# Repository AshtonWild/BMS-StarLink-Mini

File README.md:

# 5S 26650 BMS for Starlink Mini

A battery management board for a 5-cell (5S) Li-ion 26650 pack that powers a Starlink Mini through an IP2368 USB-C charger/converter module. Designed in KiCad 10.

This board was designed specifically for the [Nexus-2 (Mounted Pack)](https://eclecticdesigns.ca/shop/p/nexus-2) from [eclecticdesigns.ca](https://eclecticdesigns.ca). Its shape, mounting holes and wire-pad positions are laid out for that pack, so check the fit before using it in anything else.

Designed by Ashton W, Eclectic Designs Inc. Board revision: **Rev 2026-11-03**.

| Bottom (components) | Top (cell wire pads) |
|---|---|
|  |  |

> **Lithium battery warning.** A 5S 26650 pack can deliver hundreds of amps into a short and can catch fire if overcharged, shorted, or charged below freezing. This is a hobby design shared as-is, with no warranty. It has not been certified or independently tested. Build and use it at your own risk, never leave a first charge unattended, and follow [docs/TESTING.md](docs/TESTING.md) before connecting real cells.

## Read this first: known issues in this revision

The design files and BOM in this repository are **Rev 2026-11-03 as drawn**. A later design review found two parts that must be substituted when you build it. Both use the existing pads; the PCB does not change.

| Part | As drawn | Fit instead | Why |
|---|---|---|---|
| **U1** | BM3451TJDC-T28A | BM3451**TNDC**-T28A or BM3451**UNDC**-T28A | The TJDC version is obsolete. The others are pin-compatible. |
| **D1** | SMCJ24CA (two-way TVS) | SMCJ24**A** (one-way TVS), **turned 180° from the board marking** | The two-way part lets the FETs see too much voltage when a short is cut off. |

**D1 orientation is safety-critical.** The cathode band must be on the pad connected to PACK+. Fitted the other way round, it shorts the pack. See [docs/ASSEMBLY.md](docs/ASSEMBLY.md).

Other limitations to know about:

- **No cold-charge protection.** The BM3451 has no low-temperature cut-off. Use the IP2368's NTC input with a thermistor on the cells.
- **TH1 is on the board, not on a cell.** Use a leaded thermistor taped to a cell instead.
- **No strain relief** for the battery wires. Glue them down after soldering.
- **No test points.** Probe on component pads.

The full review is in [docs/DESIGN_REVIEW.txt](docs/DESIGN_REVIEW.txt).

## Specifications

| | |
|---|---|
| Cells | 5 in series, Li-ion 26650 (4.2 V full) |
| Protection IC | BYD BM3451 (TSSOP-28) |
| Overcharge cut-off | 4.25 V per cell (TNDC) or 4.235 V (UNDC), 1 s delay |
| Low-voltage cut-off | 2.8 V per cell (TNDC/UNDC), 1 s delay |
| Discharge overcurrent | about 20 A (200 ms), 80 A (4.4 ms), 160 A short circuit (about 300 µs) |
| Charge overcurrent | about 10 A |
| Intended load | about 7 A continuous |
| Cell balancing | passive, about 89 mA per cell, starts at about 4.19 V |
| Over-temperature | charge off at about 45 °C, discharge off at about 62 °C (10 kΩ B3950 NTC) |
| Fuse | Littelfuse 0456025.ER, 25 A, on the positive output |
| Power FETs | 2 × Vishay SiR638ADP (40 V), low side, back to back |
| Current sense | 5 mΩ, 3 W, Kelvin connected |
| Board | 2 layers, 2 oz copper, 1.6 mm, about 155 × 85 mm overall, 4 × M3 holes |

Trip currents come from the BM3451 datasheet thresholds and the 5 mΩ sense resistor; allow about ±15–20%.

## Repository layout

```
hardware/     KiCad 10 project (schematic, PCB, custom footprints, design rules)
production/   Gerbers, BOM and placement file as sent to JLCPCB
docs/         Schematic PDF, board prints, assembly guide, test procedure, design review
```

| File | What it is |
|---|---|
| `hardware/BMS StarLink Mini.kicad_pro` | Open this in KiCad 10 |
| `production/BMS_StarLink_Mini_Gerbers_JLCPCB.zip` | Gerber and drill files |
| `production/BMS_StarLink_Mini_BOM_JLCPCB.csv` / `.xlsx` | BOM with LCSC part numbers |
| `production/BMS_StarLink_Mini_CPL_JLCPCB.csv` | Component placement file |
| `docs/schematic.pdf` | Schematic |
| `docs/pcb-top.pdf`, `docs/pcb-bottom.pdf` | Copper and silkscreen prints (bottom is mirrored, as viewed from the bottom) |
| `docs/ASSEMBLY.md` | Ordering, part substitutions, wiring |
| `docs/TESTING.md` | Bring-up and test procedure |
| `docs/DESIGN_REVIEW.txt` | Review findings and where to buy replacement parts |

## Ordering the board

Settings used for JLCPCB:

- 2 layers, **2 oz outer copper**, **1.6 mm** thickness
- Surface finish: HASL lead-free or ENIG
- Assembly: bottom side (48 parts). TH1 is the only top-side part.

The design rules in the project match JLCPCB's 2 oz limits (0.16 mm track and clearance, 0.2 mm via to track). The board passes DRC with 0 violations and matches the schematic.

When you upload the BOM, change U1 and D1 as described above, or leave both unplaced and solder them by hand. Check the placement preview for rotation of U1, Q1–Q7, D1 and F1 before paying.

## Building and testing

1. Order the board and parts: [docs/ASSEMBLY.md](docs/ASSEMBLY.md)
2. Test the bare board on a bench supply, then with cells: [docs/TESTING.md](docs/TESTING.md)

## Datasheets

- [BYD BM3451](https://www.bydmicro.com/params/field/preview/PDF_PRODUCT_202304141002.pdf)
- [Vishay SiR638ADP](https://www.vishay.com/en/product/75297)

## License

No license has been chosen yet. Until one is added, the files are published for reference only.

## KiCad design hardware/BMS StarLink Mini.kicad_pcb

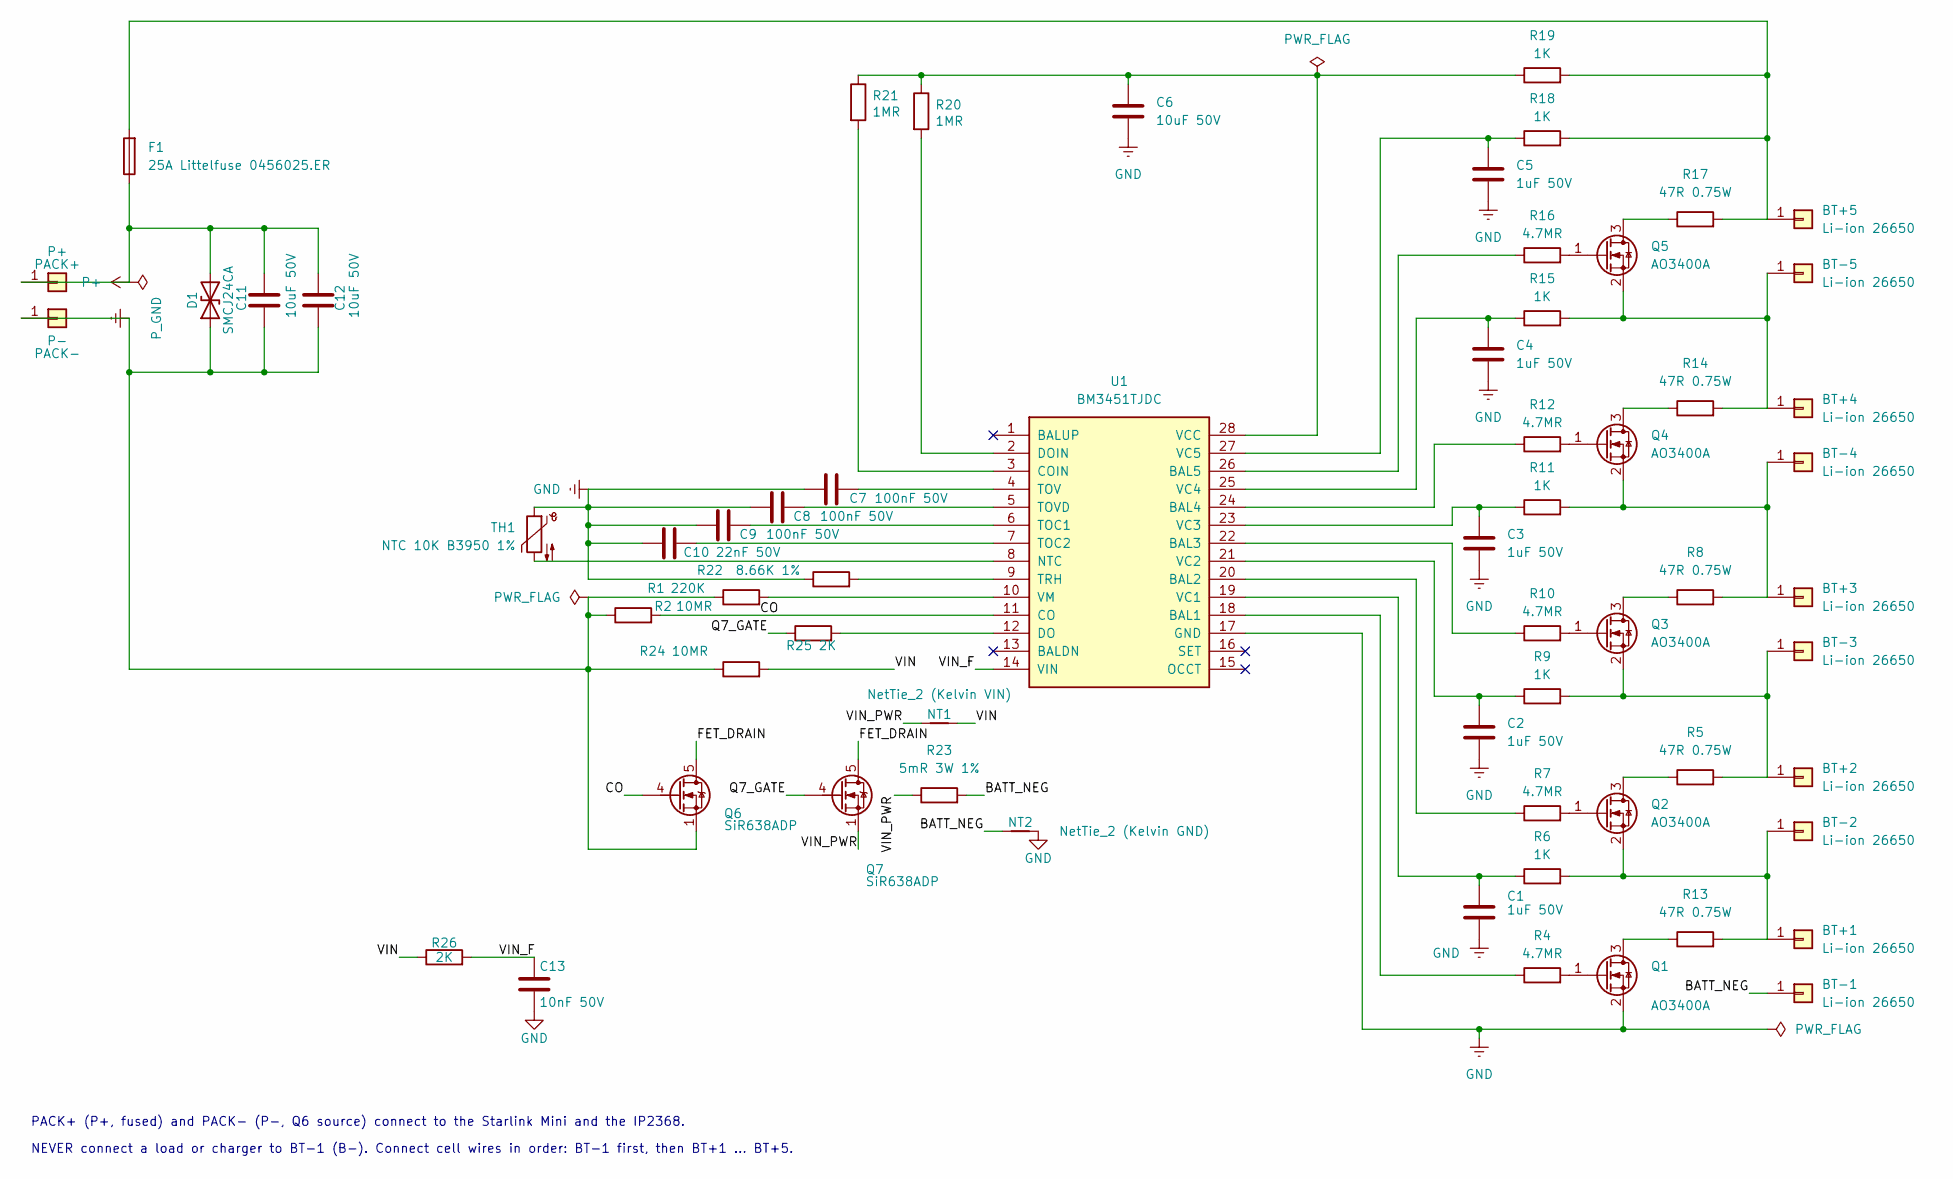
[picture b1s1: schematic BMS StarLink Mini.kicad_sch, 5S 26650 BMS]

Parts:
BT+1, BT+2, BT+3, BT+4, BT+5: Li-ion 26650; WirePad_SMD_5x8mm_2.5sqmm
BT-1, BT-2, BT-3, BT-4, BT-5: Li-ion 26650; WirePad_SMD_5x8mm_2.5sqmm
C1, C2, C3, C4, C5: 1uF 50V; C_0805_2012Metric; LCSC C28323
C6, C11, C12: 10uF 50V; C_1210_3225Metric; MPN CL32B106KBJNNNE; LCSC C138687
C7, C8, C9: 100nF 50V; C_0603_1608Metric; LCSC C14663
C10: 22nF 50V; C_0603_1608Metric; LCSC C21122
C13: 10nF 50V; C_0603_1608Metric; LCSC C57112
D1: SMCJ24CA; D_SMC; MPN SMCJ24CA; LCSC C3040015
F1: 25A Littelfuse 0456025.ER; Fuse_Littelfuse_456_NANO2_20A-30A; MPN 0456025.ER; LCSC C315877
NT1: NetTie_2 (Kelvin VIN); NetTie-2_SMD_Pad0.5mm
NT2: NetTie_2 (Kelvin GND); NetTie-2_SMD_Pad0.5mm
P+: PACK+; WirePad_SMD_6x9mm_2.5sqmm
P-: PACK-; WirePad_SMD_6x9mm_2.5sqmm
Q1, Q2, Q3, Q4, Q5: AO3400A; SOT-23; LCSC C20917
Q6, Q7: SiR638ADP; PowerPAK_SO-8_Single; MPN SIR638ADP-T1-RE3; LCSC C3279537
R1: 220K; R_0603_1608Metric; LCSC C22961
R2, R24: 10MR; R_0603_1608Metric; LCSC C7250
R4, R7, R10, R12, R16: 4.7MR; R_0603_1608Metric; LCSC C23163
R5, R8, R13, R14, R17: 47R 0.75W; R_2010_5025Metric; LCSC C174983
R6, R9, R11, R15, R18: 1K; R_0603_1608Metric; LCSC C21190
R19: 1K; R_1206_3216Metric; LCSC C4410
R20, R21: 1MR; R_0603_1608Metric; LCSC C22935
R22: 8.66K 1%; R_0603_1608Metric; LCSC C101218
R23: 5mR 3W 1%; R_2512_6332Metric; LCSC C154688
R25, R26: 2K; R_0603_1608Metric; LCSC C22975
TH1: NTC 10K B3950 1%; R_0603_1608Metric; LCSC C2892547
U1: BM3451TJDC; TSSOP-28_4.4x9.7mm_P0.65mm; LCSC C5343512

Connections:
/BATT_NEG: BT-1.1, NT2.1, R23.2
/CO: Q6.4 (G), R2.2, U1.11 (CO)
/FET_DRAIN: Q6.5 (D), Q7.5 (D)
/Q7_GATE: Q7.4 (G), R25.1
/VIN: NT1.2, R24.2, R26.1
/VIN_F: C13.1, R26.2, U1.14 (VIN)
/VIN_PWR: NT1.1, Q7.1 (S), Q7.2 (S), Q7.3 (S), R23.1
GND: C1.2, C2.2, C3.2, C4.2, C5.2, C6.2, C7.2, C8.1, C9.1, C10.1, C13.2, NT2.2, Q1.2 (S), R22.1, TH1.1, U1.17 (GND)
unnamed: BT+1.1, BT-2.1, Q2.2 (S), R6.2, R13.2
unnamed: BT+2.1, BT-3.1, Q3.2 (S), R5.2, R9.2
unnamed: BT+3.1, BT-4.1, Q4.2 (S), R8.2, R11.2
unnamed: BT+4.1, BT-5.1, Q5.2 (S), R14.2, R15.2
unnamed: BT+5.1, F1.2, R17.2, R18.2, R19.2
unnamed: Q1.3 (D), R13.1
unnamed: Q1.1 (G), R4.2
unnamed: Q2.3 (D), R5.1
unnamed: Q2.1 (G), R7.2
unnamed: Q3.3 (D), R8.1
unnamed: Q3.1 (G), R10.2
unnamed: Q4.3 (D), R14.1
unnamed: Q4.1 (G), R12.2
unnamed: Q5.3 (D), R17.1
unnamed: Q5.1 (G), R16.2
unnamed: R4.1, U1.18 (BAL1)
unnamed: R7.1, U1.20 (BAL2)
unnamed: R10.1, U1.22 (BAL3)
unnamed: R12.1, U1.24 (BAL4)
unnamed: R16.1, U1.26 (BAL5)
unnamed: R21.2, U1.3 (COIN)
unnamed: R25.2, U1.12 (DO)
unnamed: R20.2, U1.2 (DOIN)
unnamed: TH1.2, U1.8 (NTC)
unnamed: C9.2, U1.6 (TOC1)
unnamed: C10.2, U1.7 (TOC2)
unnamed: C7.1, U1.4 (TOV)
unnamed: C8.2, U1.5 (TOVD)
unnamed: R22.2, U1.9 (TRH)
unnamed: C1.1, R6.1, U1.19 (VC1)
unnamed: C2.1, R9.1, U1.21 (VC2)
unnamed: C3.1, R11.1, U1.23 (VC3)
unnamed: C4.1, R15.1, U1.25 (VC4)
unnamed: C5.1, R18.1, U1.27 (VC5)
unnamed: C6.1, R19.1, R20.1, R21.1, U1.28 (VCC)
unnamed: R1.2, U1.10 (VM)
P+: C11.1, C12.1, D1.2 (A2), F1.1, P+.1
P_GND: C11.2, C12.2, D1.1 (A1), P-.1, Q6.1 (S), Q6.2 (S), Q6.3 (S), R1.1, R2.1, R24.1

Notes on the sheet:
PACK+ (P+, fused) and PACK- (P-, Q6 source) connect to the Starlink Mini and the IP2368.
NEVER connect a load or charger to BT-1 (B-). Connect cell wires in order: BT-1 first, then BT+1 ... BT+5.

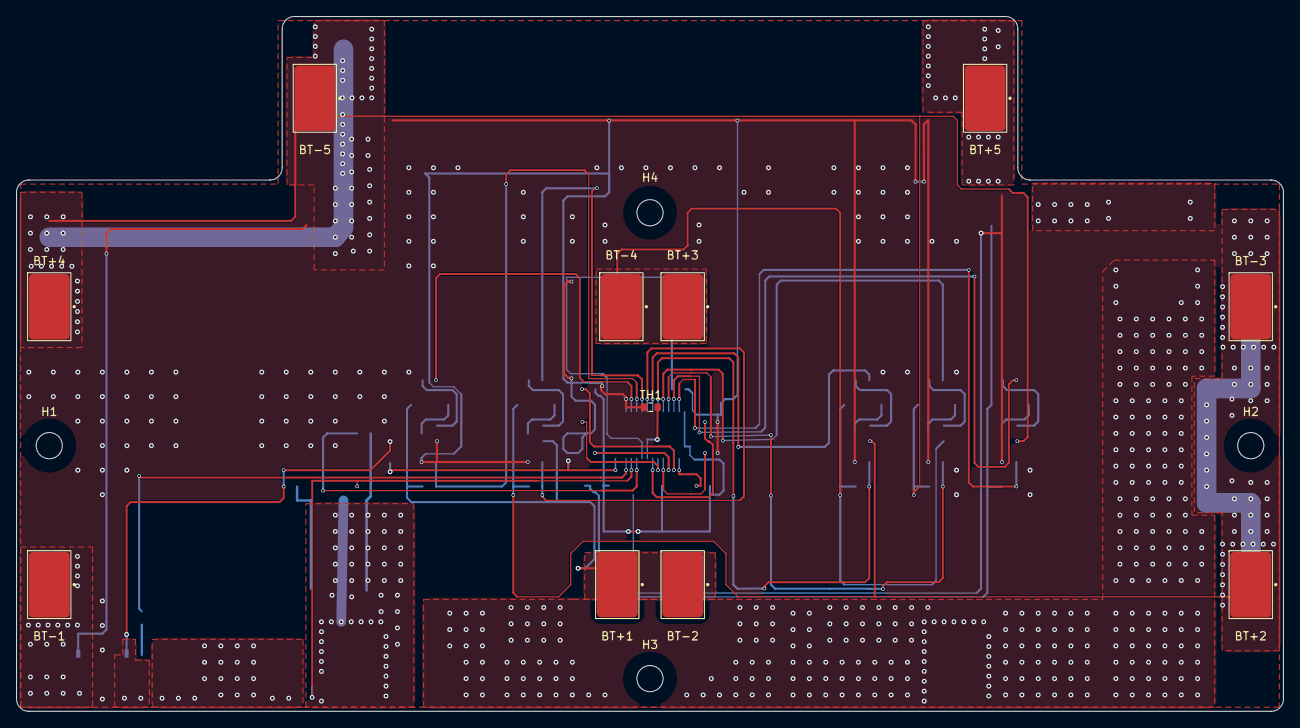
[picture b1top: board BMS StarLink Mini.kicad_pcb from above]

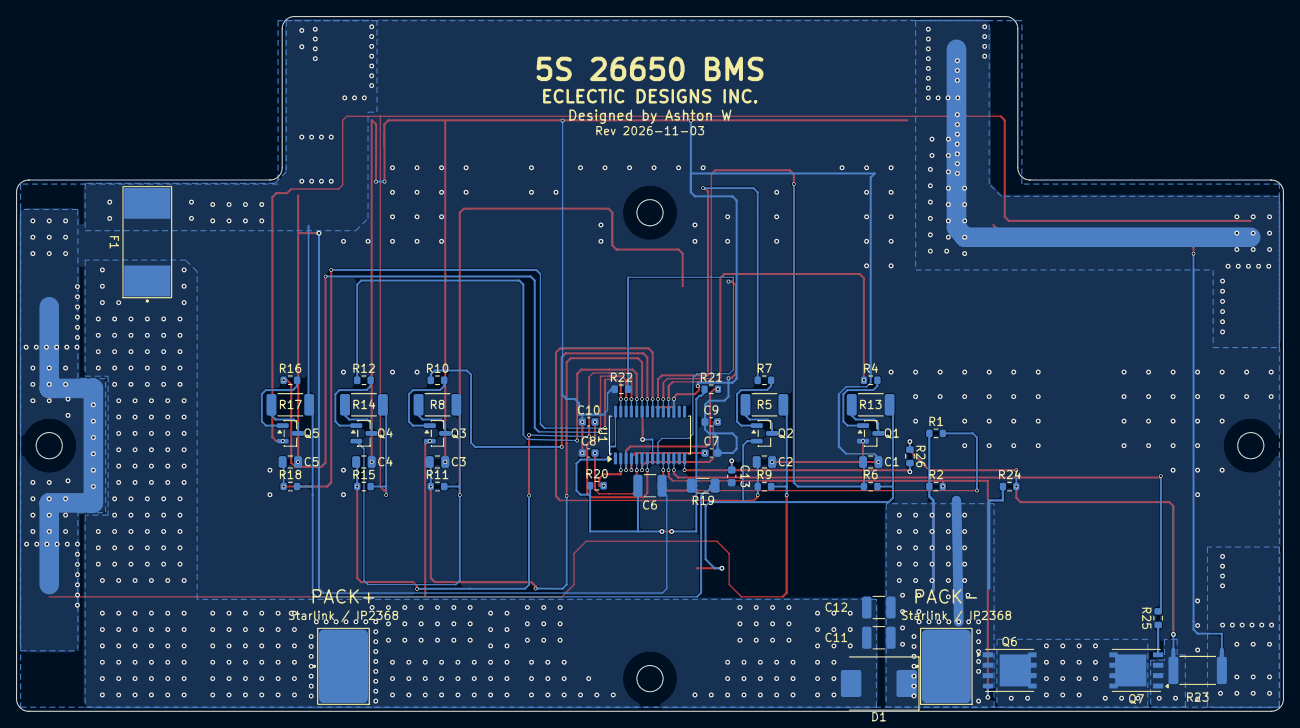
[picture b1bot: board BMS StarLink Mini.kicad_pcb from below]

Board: 2 copper layers, 155.0 x 85.0 mm, 67 parts (52 on the bottom side), 46 nets.

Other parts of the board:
H1, H2, H3, H4: MountingHole_3.2mm_M3

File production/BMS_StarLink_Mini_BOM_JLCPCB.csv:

"Comment","Designator","Footprint","LCSC Part #"
"1uF 50V","C1,C2,C3,C4,C5","Capacitor_SMD:C_0805_2012Metric","C28323"
"10uF 50V","C6,C11,C12","Capacitor_SMD:C_1210_3225Metric","C138687"
"100nF 50V","C7,C8,C9","Capacitor_SMD:C_0603_1608Metric","C14663"
"22nF 50V","C10","Capacitor_SMD:C_0603_1608Metric","C21122"
"10nF 50V","C13","Capacitor_SMD:C_0603_1608Metric","C57112"
"SMCJ24CA","D1","Diode_SMD:D_SMC","C3040015"
"25A Littelfuse 0456025.ER","F1","BMS_StarLink:Fuse_Littelfuse_456_NANO2_20A-30A","C315877"
"AO3400A","Q1,Q2,Q3,Q4,Q5","Package_TO_SOT_SMD:SOT-23","C20917"
"SiR638ADP","Q6,Q7","Package_SO:PowerPAK_SO-8_Single","C3279537"
"220K","R1","Resistor_SMD:R_0603_1608Metric","C22961"
"10MR","R2,R24","Resistor_SMD:R_0603_1608Metric","C7250"
"4.7MR","R4,R7,R10,R12,R16","Resistor_SMD:R_0603_1608Metric","C23163"
"47R 0.75W","R5,R8,R13,R14,R17","Resistor_SMD:R_2010_5025Metric","C174983"
"1K","R6,R9,R11,R15,R18","Resistor_SMD:R_0603_1608Metric","C21190"
"1K","R19","Resistor_SMD:R_1206_3216Metric","C4410"
"1MR","R20,R21","Resistor_SMD:R_0603_1608Metric","C22935"
"8.66K 1%","R22","Resistor_SMD:R_0603_1608Metric","C101218"
"5mR 3W 1%","R23","Resistor_SMD:R_2512_6332Metric","C154688"
"2K","R25,R26","Resistor_SMD:R_0603_1608Metric","C22975"
"NTC 10K B3950 1%","TH1","Resistor_SMD:R_0603_1608Metric","C2892547"
"BM3451TJDC","U1","Package_SO:TSSOP-28_4.4x9.7mm_P0.65mm","C5343512"
